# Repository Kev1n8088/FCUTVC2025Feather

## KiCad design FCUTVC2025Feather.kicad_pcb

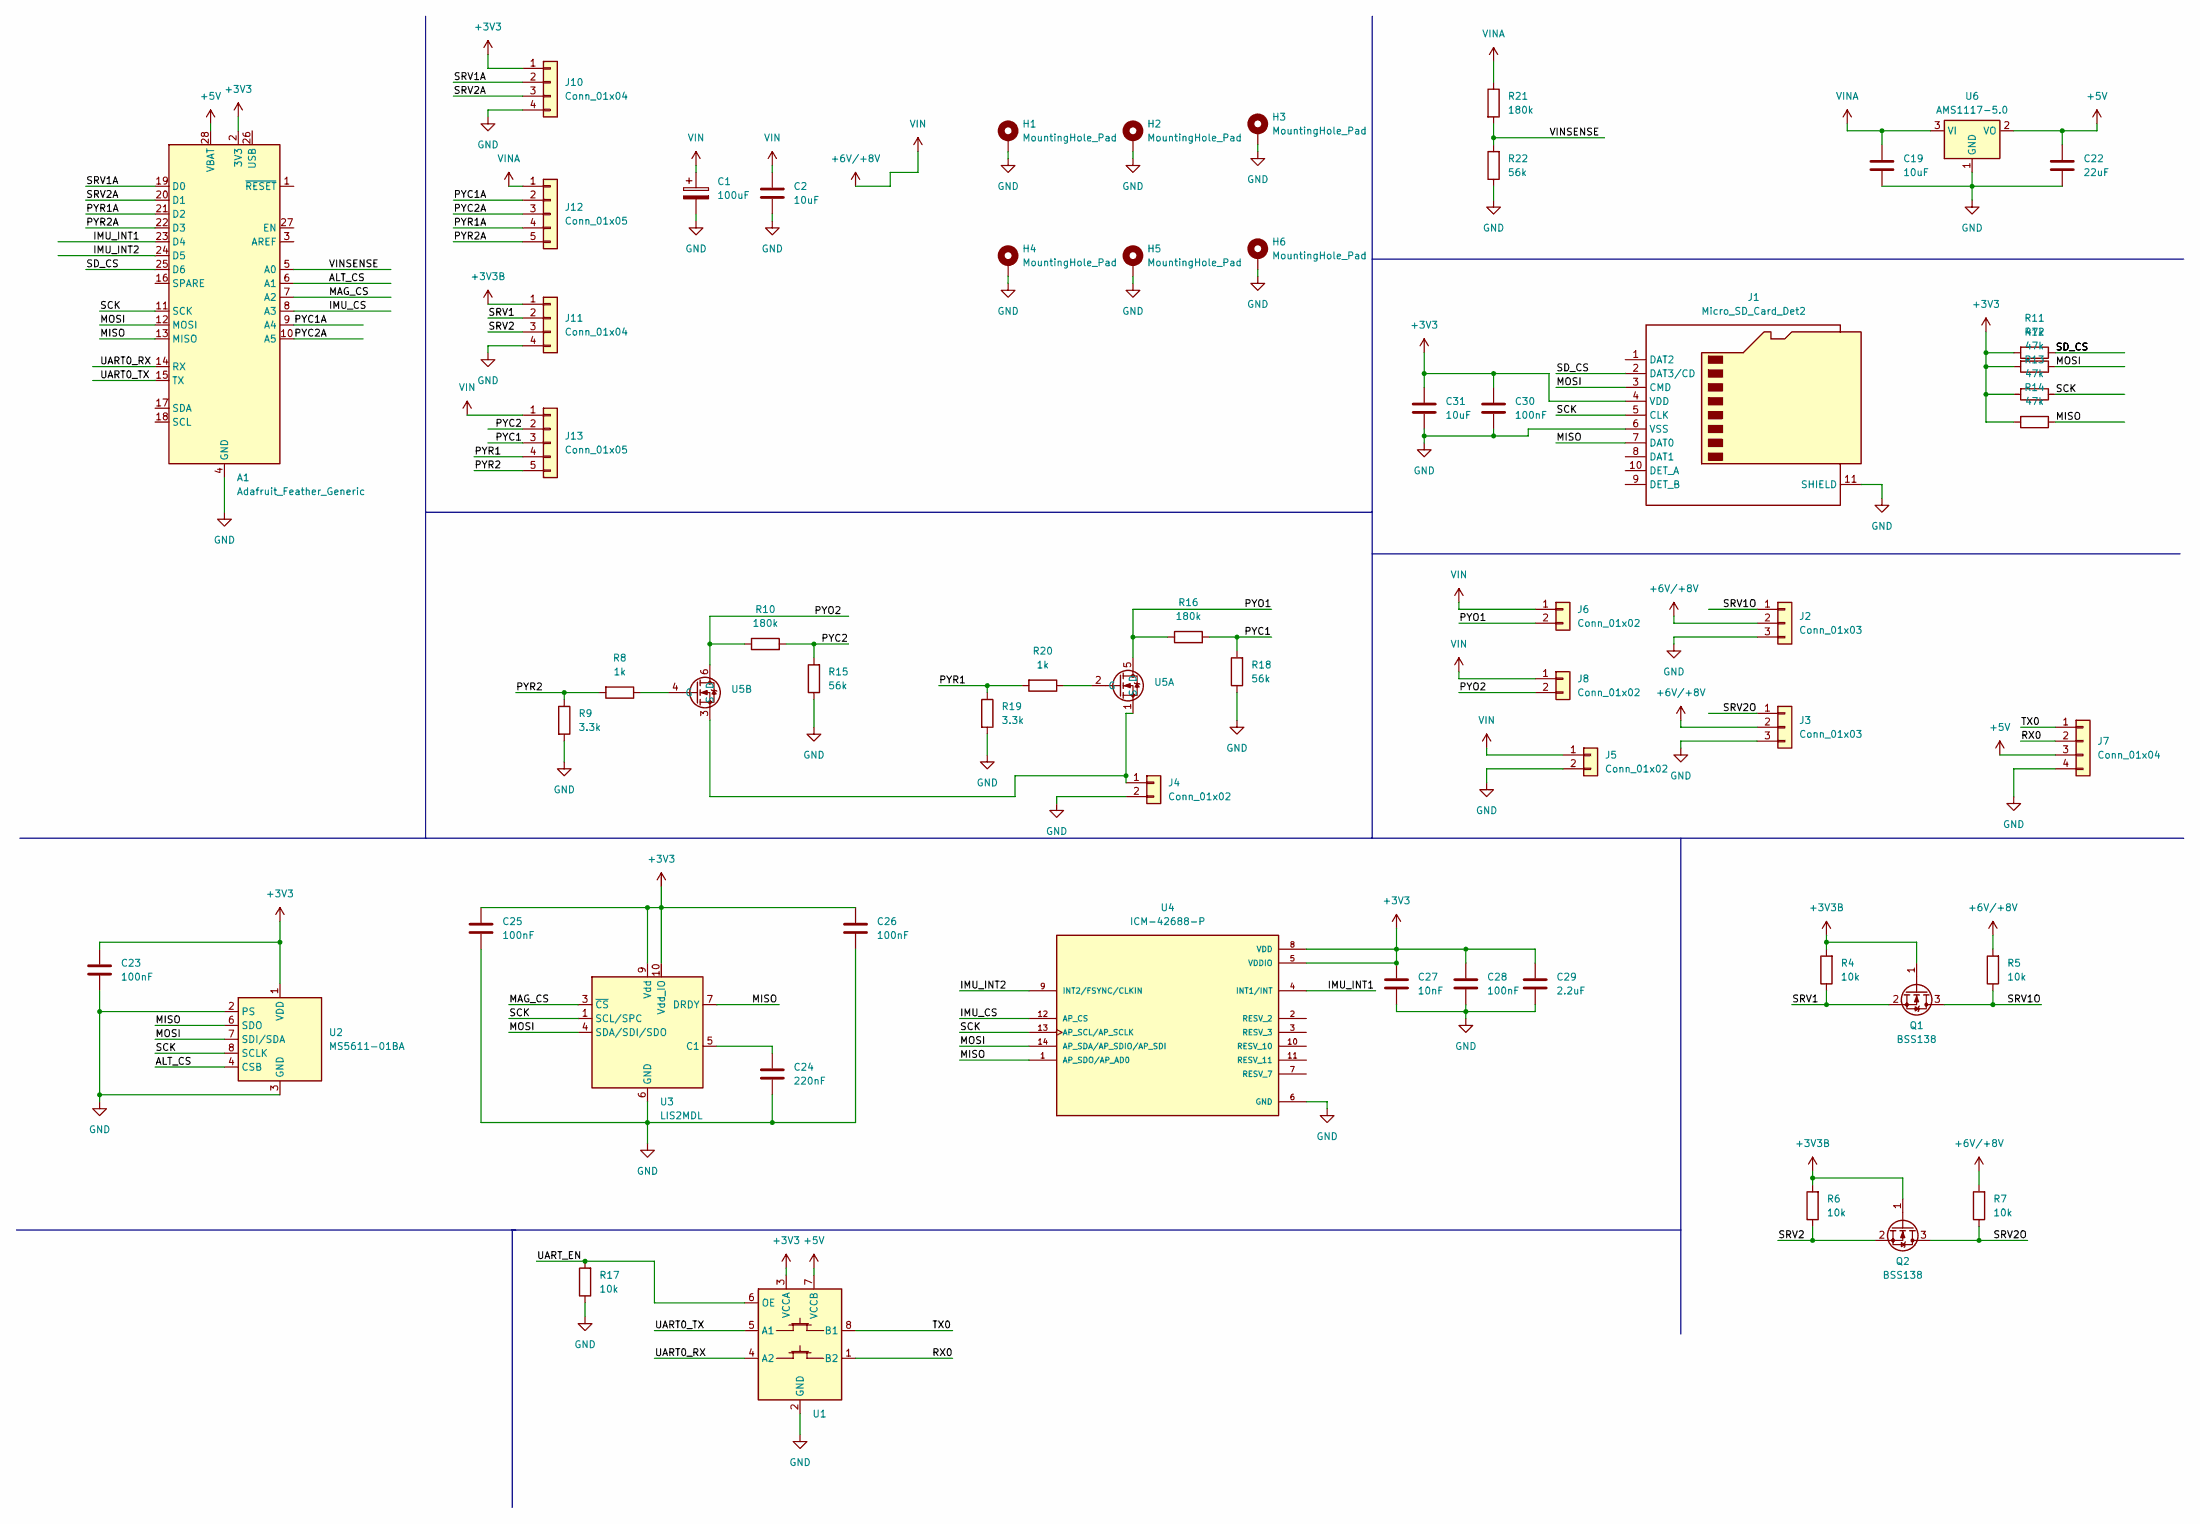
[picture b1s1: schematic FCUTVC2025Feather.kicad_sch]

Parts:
A1: Adafruit_Feather_Generic; Adafruit_Feather
C1: 100uF; CP_Elec_6.3x7.7
C2, C19, C31: 10uF; C_0402_1005Metric
C22: 22uF; C_0402_1005Metric
C23, C25, C26, C28, C30: 100nF; C_0402_1005Metric
C24: 220nF; C_0402_1005Metric
C27: 10nF; C_0402_1005Metric
C29: 2.2uF; C_0402_1005Metric
H1, H2, H3, H4, H5, H6: MountingHole_Pad; MountingHole_4.3mm_M4_DIN965_Pad_TopBottom
J1: Micro_SD_Card_Det2; microSD_HC_Hirose_DM3BT-DSF-PEJS
J2, J3: Conn_01x03; JST_XH_B3B-XH-AM_1x03_P2.50mm_Vertical
J4, J6, J8: Conn_01x02; JST_XH_B2B-XH-AM_1x02_P2.50mm_Vertical
J5: Conn_01x02; AMASS_XT30U-M_1x02_P5.0mm_Vertical
J7: Conn_01x04; JST_PH_B4B-PH-K_1x04_P2.00mm_Vertical
J10, J11: Conn_01x04; PinHeader_1x04_P2.54mm_Vertical
J12, J13: Conn_01x05; PinHeader_1x05_P2.54mm_Vertical
Q1, Q2: BSS138; SOT-23
R4, R5, R6, R7, R17: 10k; R_0402_1005Metric
R8, R20: 1k; R_0402_1005Metric
R9, R19: 3.3k; R_0402_1005Metric
R10, R16, R21: 180k; R_0402_1005Metric
R11, R12, R13, R14: 47k; R_0402_1005Metric
R15, R18, R22: 56k; R_0402_1005Metric
U1: TXS0102DCT; SSOP-8_2.95x2.8mm_P0.65mm
U2: MS5611-01BA; LGA-8_3x5mm_P1.25mm
U3: LIS2MDL; LGA-12_2x2mm_P0.5mm
U4: ICM-42688-P; PQFN50P300X250X97-14N; PARTREV 1.2
U5: SQJ500AEP-T1_GE3_VIS
U6: AMS1117-5.0; SOT-223-3_TabPin2

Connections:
+3V3: A1.2 (3V3), C23.1, C25.1, C26.1, C27.1, C28.1, C29.1, C30.1, C31.1, J1.4 (VDD), J10.1, R11.2, R12.2, R13.2, R14.2, U1.3 (VCCA), U2.1 (VDD), U3.9 (Vdd), U3.10 (Vdd_IO), U4.5 (VDDIO), U4.8 (VDD)
+3V3B: J11.1, Q1.1 (G), Q2.1 (G), R4.2, R6.2
+5V: A1.28 (VBAT), C22.1, J7.3, U1.7 (VCCB), U6.2 (VO)
+6V/+8V: C1.1, C2.1, J2.2, J3.2, J5.1, J6.1, J8.1, J13.1, R5.2, R7.2
/ALT_CS: A1.6 (A1), U2.4 (CSB), U2.5 (CSB)
/IMU_CS: A1.8 (A3), U4.12 (AP_CS)
/IMU_INT1: A1.23 (D4), U4.4 (INT1/INT)
/IMU_INT2: A1.24 (D5), U4.9 (INT2/FSYNC/CLKIN)
/MAG_CS: A1.7 (A2), U3.3 (~CS)
/MISO: A1.13 (MISO), J1.7 (DAT0), R14.1, U2.6 (SDO), U3.7 (DRDY), U4.1 (AP_SDO/AP_AD0)
/MOSI: A1.12 (MOSI), J1.3 (CMD), R12.1, U2.7 (SDI/SDA), U3.4 (SDA/SDI/SDO), U4.14 (AP_SDA/AP_SDIO/AP_SDI)
/PYC1: J13.3, R16.2, R18.2
/PYC1A: A1.9 (A4), J12.2
/PYC2: J13.2, R10.2, R15.2
/PYC2A: A1.10 (A5), J12.3
/PYO1: J6.2, R16.1, U5.5 (D)
/PYO2: J8.2, R10.1, U5.6 (D)
/PYR1: J13.4, R19.1, R20.2
/PYR1A: A1.21 (D2), J12.4
/PYR2: J13.5, R8.2, R9.1
/PYR2A: A1.22 (D3), J12.5
/RX0: J7.2, U1.1 (B2)
/SCK: A1.11 (SCK), J1.5 (CLK), R13.1, U2.8 (SCLK), U3.1 (SCL/SPC), U4.13 (AP_SCL/AP_SCLK)
/SD_CS: A1.25 (D6), J1.2 (DAT3/CD), R11.1
/SRV1: J11.2, Q1.2 (S), R4.1
/SRV1A: A1.19 (D0), J10.2
/SRV1O: J2.1, Q1.3 (D), R5.1
/SRV2: J11.3, Q2.2 (S), R6.1
/SRV2A: A1.20 (D1), J10.3
/SRV2O: J3.1, Q2.3 (D), R7.1
/TX0: J7.1, U1.8 (B1)
/UART0_RX: A1.14 (RX), U1.4 (A2)
/UART0_TX: A1.15 (TX), U1.5 (A1)
/UART_EN: R17.2, U1.6 (OE)
/VINSENSE: A1.5 (A0), R21.2, R22.2
GND: A1.4 (GND), C1.2, C2.2, C19.2, C22.2, C23.2, C24.2, C25.2, C26.2, C27.2, C28.2, C29.2, C30.2, C31.2, H1.1, H2.1, H3.1, H4.1, H5.1, H6.1, J1.6 (VSS), J1.11 (SHIELD), J2.3, J3.3, J4.2, J5.2, J7.4, J10.4, J11.4, R9.2, R15.1, R17.1, R18.1, R19.2, R22.1, U1.2 (GND), U2.2 (PS), U2.3 (GND), U3.6 (GND), U3.8 (GND), U4.6 (GND), U6.1 (GND)
unnamed: J4.1, U5.1 (S), U5.3 (S)
unnamed: C24.1, U3.5 (C1)
unnamed: R20.1, U5.2 (G)
unnamed: R8.1, U5.4 (G)
VINA: C19.1, J12.1, R21.1, U6.3 (VI)

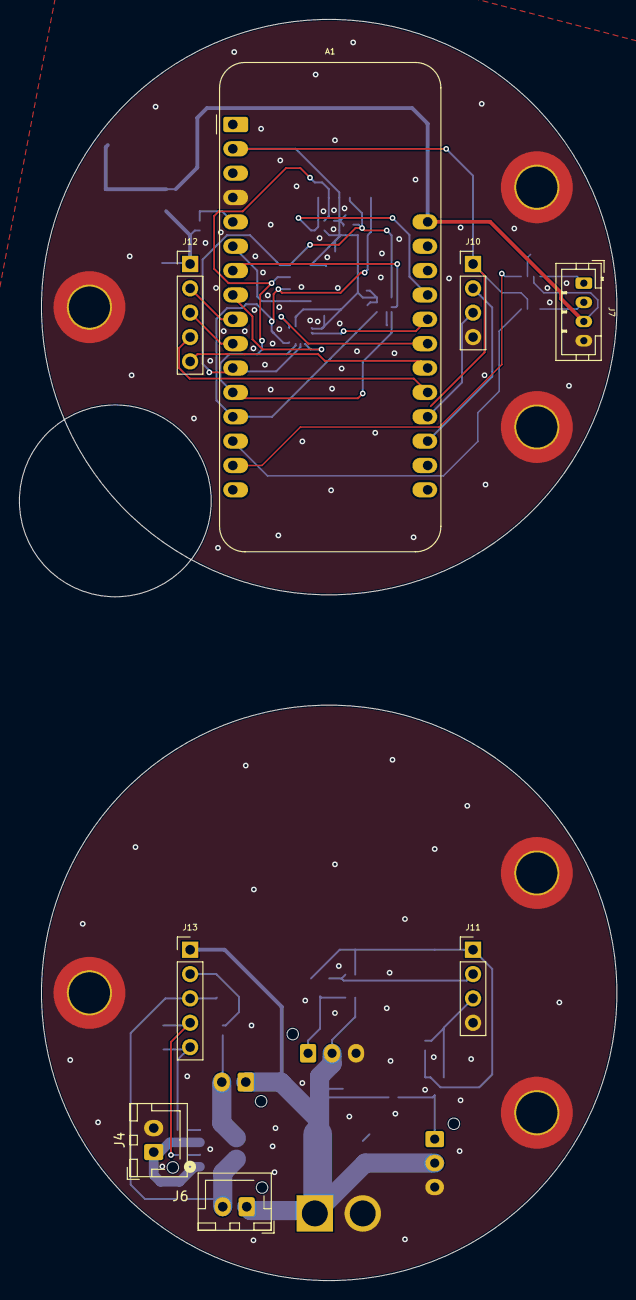
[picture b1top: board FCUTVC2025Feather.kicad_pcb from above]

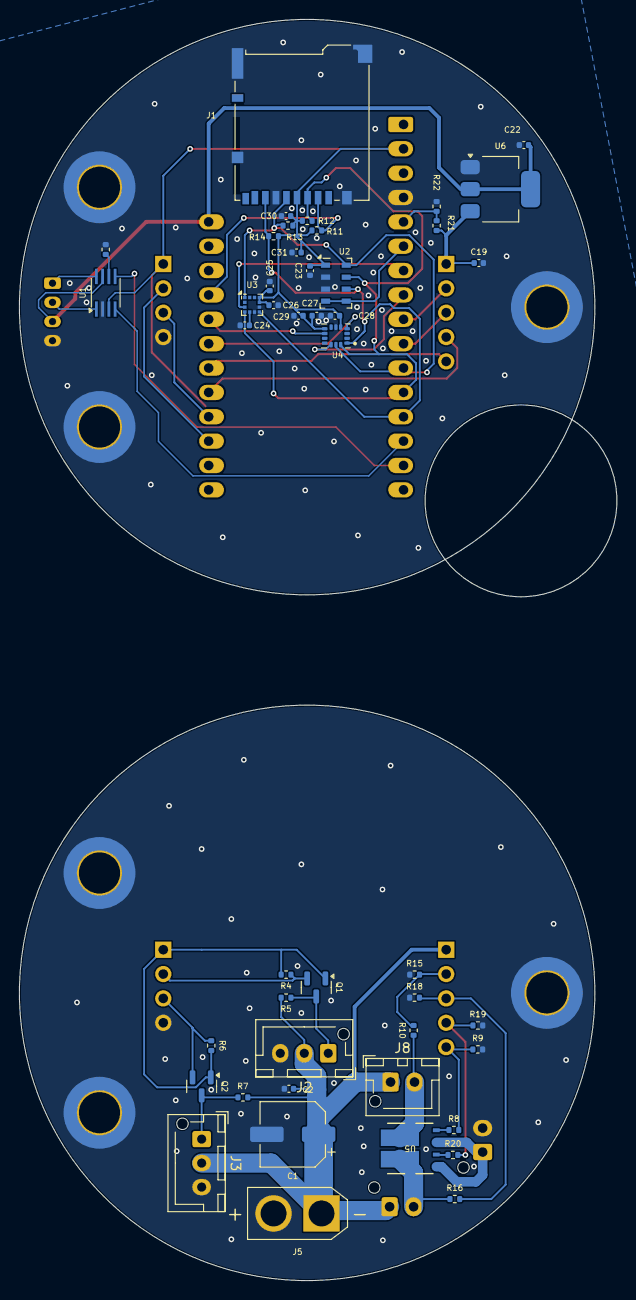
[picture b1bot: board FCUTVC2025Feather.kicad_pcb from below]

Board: 2 copper layers, 62.3 x 131.5 mm, 59 parts (45 on the bottom side), 41 nets.

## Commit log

2025-01-16 finished pcb
2025-01-16 fixed drc
2025-01-17 changed servo and pyro headers to JST XH (w/ hole). V1 complete
2025-01-17 added mounting holes (25mm 0 degrees, 150 degrees, 210 degrees)
2025-01-23 Added cut for wire routing and changed a pyro channel to facing up
